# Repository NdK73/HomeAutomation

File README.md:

# HomeAutomation

This project consists of a protocol spec, the design files for physical nodes and the source code that glues it together.

## Protocol

[Full protocol description](protocol/protocol.txt) is available, together with examples of a [monitor](protocol/dom-monitor.py) and a [sender](protocol/dom-send.py). The protocol is text-based to ease debugging.

**ClearSky technology inside**: the basic concept is that **no coordinator** is needed for the nodes to work after the initial configuration. There must not be a single point of (catastrophic) failure. And obviously no "cloud" (hence **ClearSky**) service is needed either: you, and only you, decide if/when/which data can exit from your network!

The most critical element is currently the access point, that is so cheap that having a cold-standby one should not be a problem.

Messages must support authentication and encryption to guarantee that confidential packets or dangerous commands are actually sent from an authorized source.

**Warning**: protocol is still **work in progress** and **unstable**: non-backward-compatible changes are still possible! Only after 1.0.0 milestone changes that introduce incompatibilities will be delayed till 2.0.0 .

## HW

All HW designs were in [KiCAD](https://kicad.org/) 4.0.x (will follow what's packaged in latest [Ubuntu LTS](https://www.ubuntu.com/)) so not to require nonstandard installs. But 5.x introduced too many new features not to be used, and it's "easy enough" to install ([official instructions](https://kicad.org/download/ubuntu/)).

DIN-rail mounted devices are designed for the 6-modules [AK-DR-04C enclosure](https://www.aliexpress.com/item/-/1733706262.html). **Note:** these enclosures won't fit in a standard DIN rail box, unless you can move the rail further from the front panel (like in Gewiss GW40030).

Other devices are designed to be compatible with Vimar Plana series, but should fit other series with minor adjustements.

In the given layouts I use KF2EDGK **right-angle** (KF-2P, KF-4P or KF-6P) 5.08mm (or 3.81mm) pitch connectors so I can detach the node from power without having exposed wires with dangerous voltage laying around (and can reconnect it quickly and safely). Be sure to buy the angled version or you'll have a lot of extra work to bend the pins!

**Warning**: I did my best to keep the costs down without sacrificing security. Choice of the power brick is really important for security: **never** use HLK-PM01 clones unless you know what you're doing -- and even then it's better to avoid using 'em! If in doubt buy directly from [Hi-Link](http://www.hlktech.net/) (sorry, plain http, not https...). Probably the boards can't pass CE certification [only because of conducted emissions](https://skippy.org.uk/revisiting-the-hlk-pm01/), but since I don't have access to test equipment **use at your own risk** (or have 'em certified).

SSRs and relays should always be sourced from reputable sources. If in doubt, do not load 'em near the limits. For example never try a 400W load on a 2A SSR -- use a servo-relay. 2A SSRs are good for a couple of LED lamps, or a 40W bulb.

### [DomoNode](domonode) 1.1

A node based on ESP8266 to be mounted in a 6-modules DIN rail enclosure.

Provides 4 SSR outputs and an expansion bus connector.

[OSHW] IT000001 | [Certified open source hardware](https://oshwa.org/cert)

#### Errata

 - The text for GPIO4 and GPIO5 are reversed in the ESP12 symbol.

### [DomoNode 2](domonode2) 2.1 (WIP)

Evolution of DomoNode, but offers 6 inputs @ 230V, 6 SSR 2A@230V (each one have its own independent in and out lines, for maximum flexibility) and 8 independent LEDs, still in a 6-modules DIN rail enclosure. Kept SW compatibility with basic DomoNode (just the first 4 outputs), but different external connections.

To better follow the norms, now inputs are on the top and outputs at the bottom.

Same expansion bus connector as the DomoNode 1.1.

I kept 2mm between L and N lines and it **ought** to be double-insulation, but it's actually not required: the user can't touch anything that is not already expected to be at 230V (screws in connectors) without opening the enclosure (the expansion connector **MUST NOT** be exposed).

The board requires two v-cuts around the central part, drawn on ECO2 layer (but not visible in the image). Once the two boards gets separated, the smaller one have to be mounted over the bigger one, using 2 M3x25mm **plastic** spacers and suitable 1x14 pins headers (I used 2 1x14 female headers on the boards and 1x14 male pin strip with 21mm long pins to connect the two headers).

**Notes**:
 - Designed in KiCAD 5.1.5.
 - You can probably omit C8 quite safely

#### Errata

 - **Use 1k for R15-R22** or D1-D8 will burn after some months of use

#### Changes from (deprecated) [2.0](domonode2.0)
 - No glitches at powerup on outputs: all outputs are off until told otherwise by FW
 - Uses PCA9555 instead of MCP23017 (smaller, cheaper and already used for other expanders = smaller code footprint)
 - PCA9555 requires less components (pullups are included and outputs can directly drive SSRs)
 - wider traces (6mils were really too thin)
 - added socket for authentication chip (ATSHA204A or ATECC608A)
 - slightly moved connectors to better fit enclosure; probably some extra cuts to better accomodate connectors will be required anyway
 - replaced through-hole LEDs with SMD 0805 ones, better suited for light guides
 - highlighted pin 1 side for SMD IC footprints
 - corrected SDA and SCL pin assignment to use Wire.begin()
 - reduced confusing level semantics: relays and LEDs are ON when writing a HIGH level to the port (required to keep compatibility with FW for DomoNode 1.1), inputs are active when reading a LOW level (can be inverted via PCA9555)
 - used the PCB part with JLCPCB order number as a guide for LED holes: align "BASE" to the bottom of the concave part at the top of the box cover and use "LEDS CNTR" line to mark LEDs center line, then rotate the ruler and use markers on the short edges as a reference for the center line of the holes (the side opposite to "BASE" must be in contact with the right side of the concave part)
 - includes (yet untested) lightguides design files, ready to be sent to laser cutting service (use 5mm transparent plexiglas)
 - includes sample code (just add your FSM; webserver already accepts clicks on relay status to toggle it; config editing not yet implemented)

### [DomoNode-inout](domonode-inout) 1.1.1

An expansion node to be mounted in a 6-modules DIN rail enclosure.

Provides 4 SSR outputs, 3 220V opto-isolated inputs and 8 5V GPIOs.

Uses a PCA9555 for GPIOs and a 24C02 to store the expander config.

[OSHW] IT000002 | [Certified open source hardware](https://oshwa.org/cert)

### [DomoDisp](domodisp) 1.1

A node based on ESP8266 that provides physical user interface to the system.
Uses a 1.8" ST7735 LCD color display and a rotative encoder.
It is designed to be mounted either on the front of a DIN rail box, inside
a 4-modules Vimar Plana frame -- other frames could work but are untested, or
with the supplied enclosure in a 504 (4-modules) wall box.

Requires a 5V power source (possibly a DomoNode-inout, but a dedicated module
with power and relay will be published as soon as it's ready).

Includes sample "lib" for reading the encoder (needs cleanup... there still
are traces of experiments I did to read ESP's ADC from an interrupt routine).

The display can be managed by [TFT_eSPI](https://github.com/Bodmer/TFT_eSPI)
lib and works up to 27MHz (only 10MHz when testing on breadboard) -- remember
to edit User_setup.h before compiling your sketch!

[OSHW] IT000003 | [Certified open source hardware](https://oshwa.org/cert)

#### Errata

 - The text for GPIO4 and GPIO5 are reversed in the ESP12 symbol.

### [DomoDispV2](domodisp2) 2.0

**Future** release using shared SPI bus for display, freeing 2 GPIOs. One of
the freed GPIOs is used to control dimming.

**WARNING**: FW is incompatible with old DomoDisp!

### [DomoNode-inputs](domonode-inputs) 1.0

WIP - Still untested !

An expansion board with 11 inputs @ 220V and 5 low-voltage IOs.

When inputs are powered from 220V they get read as logic low.
Low-voltage inputs are directly connected to PCA9555 lines so there's a weak
(100k) pullup active at powerup. If you want to use 'em as outputs remember
to use inverted logic to avoid glitches at powerup.

### [DomoSwitch](domoswitch) 1.0

WIP / On hold (I'd need to source a suitable front panel, first)

A node that hosts 2 relays (or SSRs -- double footprint), 2 pushbuttons and 2
RGB LEDs. Split in 3 sub-boards to fit behind a 2-modules
[Vimar Plana 14042 hole cover](https://www.vimar.com/it/it/catalog/product/index/code/14042).

The buttons and LEDs are placed so that they match the markers inside the 14042
cover, simplifying the assemply.

To be compliant with SeeedFusion rules, I had to split the 3 sub boards as different designs.
Then I simply combined the sub-boards to better use the 100x100mm area. That means that for
$15 plus shipping I get 40 complete boards... I hope it doesn't require major mods!

**TODO**: support to enclose the dangerous sub-boards (I'll have to prototype it
with a 3D printer, but will need a resin cast for the final version).

### 3rd-party devices

It's obviously possible to support 3rd-party devices like SonOff, Shelly, touch switches and so on.
Reversing and further info is usually published first on [my site](https://csshl.net) (mostly Italian-only)

## SW

Still work in progress.

A sketch with [partial protocol implementation](https://github.com/NdK73/Domotic)
is under test.

Expansions (DomoNode-inout, DomoNode-inputs) are autodetected and (mostly)
autoconfigured by library. The algorithm is:
  - for each I2C bus address from 0x50 to 0x57
    - if slave found at 0x5X:
      - determine memory size:
        - try reading location 0-4 using 8-bit address (24LC02)
        - try re-reading the same locations, still using 8-bit addresses
        - both reads are equal => 8-bit addresses
        - else
          - set flag for 16-bit addresses
          - read locations 0-4 using 16-bit address (that would overwrite
          location 0 in 8-bit devices, but we already ruled out this
          is a 8-bit one...)
      - check first two bytes for 'magic' constant; if wrong, go to next
          address: not a device we can handle (possibly uninitialized)
      - read device config from it
    - if slave is not found at 0x5X, test if a slave is present at 0x2X
      (PCA9555 in DomoNode-inout 1.0)
      - if PCA9555 is found, create a fake config for 4 outs and 3 ins (TODO:
        how to handle other GPIOs?)
    - instantiate the correct device class

This algorithm assumes the memory have already been initialized.
The EEPROM must contain at least these 16 bytes:
  - 0x00 2 bytes 'magic' 0xD74A (0xD7 in 0x00 and 0x4A in 0x01)
  - 0x02 1 byte Expansion type (Official "registry" is kept in lib sources)
  - 0x03 1 byte Release code (every new HW release increments the release code)
  - 0x04 4 bytes "unique" board ID
  - 0x08 8 bytes reserved

The remaining space is used as defined by device class (usually for IO
configuration and descriptions).
The board ID must be "unique enough" so that the master node can detect that an
expansion have been changed and invalidate the old mappings.

## [Crypto HW](SecurityChips/)

I added to the repository all the informations I found re: security chips that could be used w/o signing NDAs. The list is probably incomplete.

I'm currently working on ATECC608A, trying to reverse engineer the information that would require signing NDA (why, Microchip? WHY??? you opened the docs for the 508...)

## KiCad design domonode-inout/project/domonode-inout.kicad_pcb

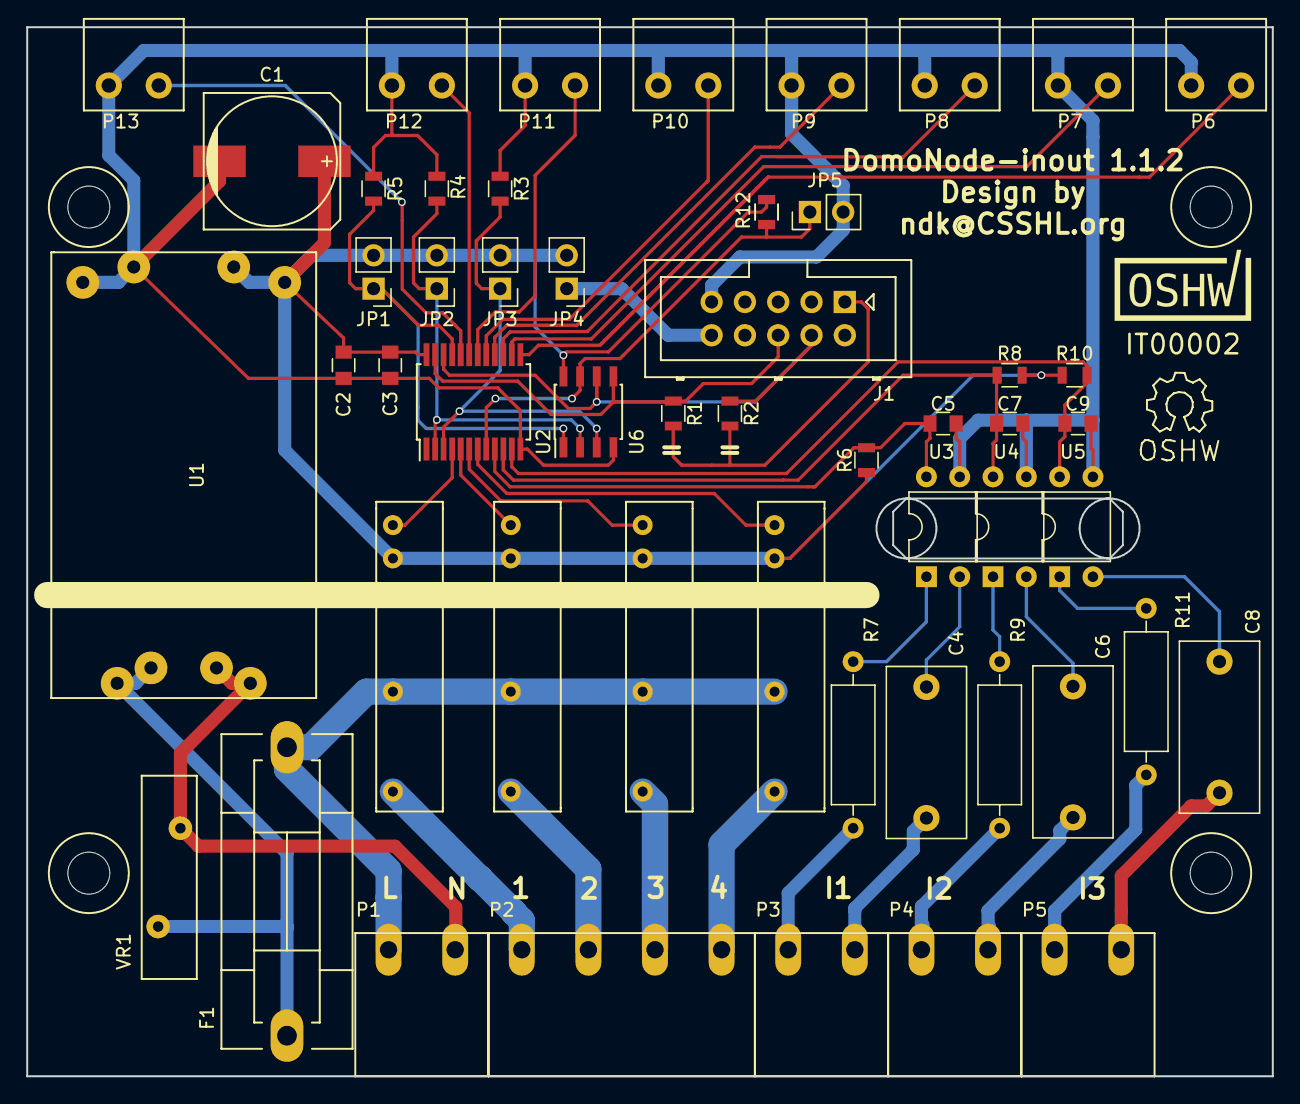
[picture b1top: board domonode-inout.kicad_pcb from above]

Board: 2 copper layers, 95.0 x 80.0 mm, 54 parts (0 on the bottom side), 44 nets.

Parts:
BOX: Enclosure_DIN_6p_nomargin
C1: C; c_elec_10x10
C2, C3: C; C_0805
C4, C6, C8: 0.1uF X2; C_Rect_L13.0mm_W6.0mm_P10.00mm_FKS3_FKP3_MKS4
C5, C7, C9: 1uF; C_0805
F1: FUSE; Fuseholder5x20_horiz_SemiClosed_Casing10x25mm
J1: CONN_2x5; Multicomp_MC9A12-1034_2x05x2.54mm_Straight
JP1, JP2, JP3: Jumper_NO_Small; Pin_Header_Straight_1x02_Pitch2.54mm
JP4, JP5: Jumper_NC_Small; Pin_Header_Straight_1x02_Pitch2.54mm
OSHW_Mono_0.25_Scale: IT00002; OSHW_Mono_0.25_Scale
P1, P3, P4, P5: CONN_01X02; KF2EDGK-5.08-2
P2: Conn_01x04; KF2EDGK-5.08-4
P6, P7, P8, P9, P10, P11, P12, P13: CONN_01X02; ScrewTerm_2x3.81_bigpads
R1, R2, R3, R4, R5, R6, R8, R10, R12: 10k; R_0805
R7, R9, R11: 1k; R_Axial_DIN0309_L9.0mm_D3.2mm_P12.70mm_Horizontal
RL1, RL2, RL3, RL4: Omron_G3MB-202; G3MB
U1: HLK-PM01; ACDC-HLK+ND
U2: PCA9555; SSOP-24_5.3x8.2mm_Pitch0.65mm
U3, U4, U5: TLP620; DIP-4_W7.62mm
U6: 24LC02; SOIC-8_3.9x4.9mm_Pitch1.27mm
VR1: VR; RV_Disc_D15.5_W4.2_P7.5

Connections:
+3V3: J1.1, R1.1, R2.1
+5V: C1.1, C2.1, C3.1, JP1.2, JP2.2, JP3.2, JP4.2, R6.1, R8.1, R10.1, R12.1, RL1.3, RL2.3, RL3.3, RL4.3, U1.4, U2.24, U6.8
/5VEXT: J1.10, JP4.1
/A0: JP1.1, R5.1, U2.21, U6.1
/A1: JP2.1, R4.1, U2.2, U6.2
/A2: JP3.1, R3.1, U2.3, U6.3
/I1L: P3.1, R7.2
/I1N: C4.2, P3.2
/I2L: P4.1, R9.2
/I2N: C6.2, P4.2
/I3L: P5.1, R11.2
/I3N: C8.2, P5.2
/IN1: C5.1, R6.2, U2.9, U3.4
/IN2: C7.1, R8.2, U2.10, U4.4
/IN3: C9.1, R10.2, U2.11, U5.4
/IO0: P6.2, U2.13
/IO1: P7.2, U2.14
/IO2: P8.2, U2.15
/IO3: P9.2, U2.16
/IO4: P10.2, U2.17
/IO5: P11.2, U2.18
/IO6: P12.2, U2.19
/IO7: P13.2, U2.20
/L: F1.2, P1.1, RL1.2, RL2.2, RL3.2, RL4.2
/N: P1.2, U1.2, VR1.1
/RL1: RL1.4, U2.4
/RL1P: P2.1, RL1.1
/RL2: RL2.4, U2.5
/RL2P: P2.2, RL2.1
/RL3: RL3.4, U2.6
/RL3P: P2.3, RL3.1
/RL4: RL4.4, U2.7
/RL4P: P2.4, RL4.1
/SCL: J1.4, R2.2, U2.22, U6.6
/SDA: J1.6, R1.2, U2.23, U6.5
/WP: JP5.1, R12.2, U2.8, U6.7
GND: C1.2, C2.2, C3.2, C5.2, C7.2, C9.2, J1.9, JP5.2, P6.1, P7.1, P8.1, P9.1, P10.1, P11.1, P12.1, P13.1, R3.2, R4.2, R5.2, U1.3, U2.12, U3.3, U4.3, U5.3, U6.4
unnamed: C4.1, U3.2
unnamed: C6.1, U4.2
unnamed: C8.1, U5.2
unnamed: F1.1, U1.1, VR1.2
unnamed: R7.1, U3.1
unnamed: R9.1, U4.1
unnamed: R11.1, U5.1

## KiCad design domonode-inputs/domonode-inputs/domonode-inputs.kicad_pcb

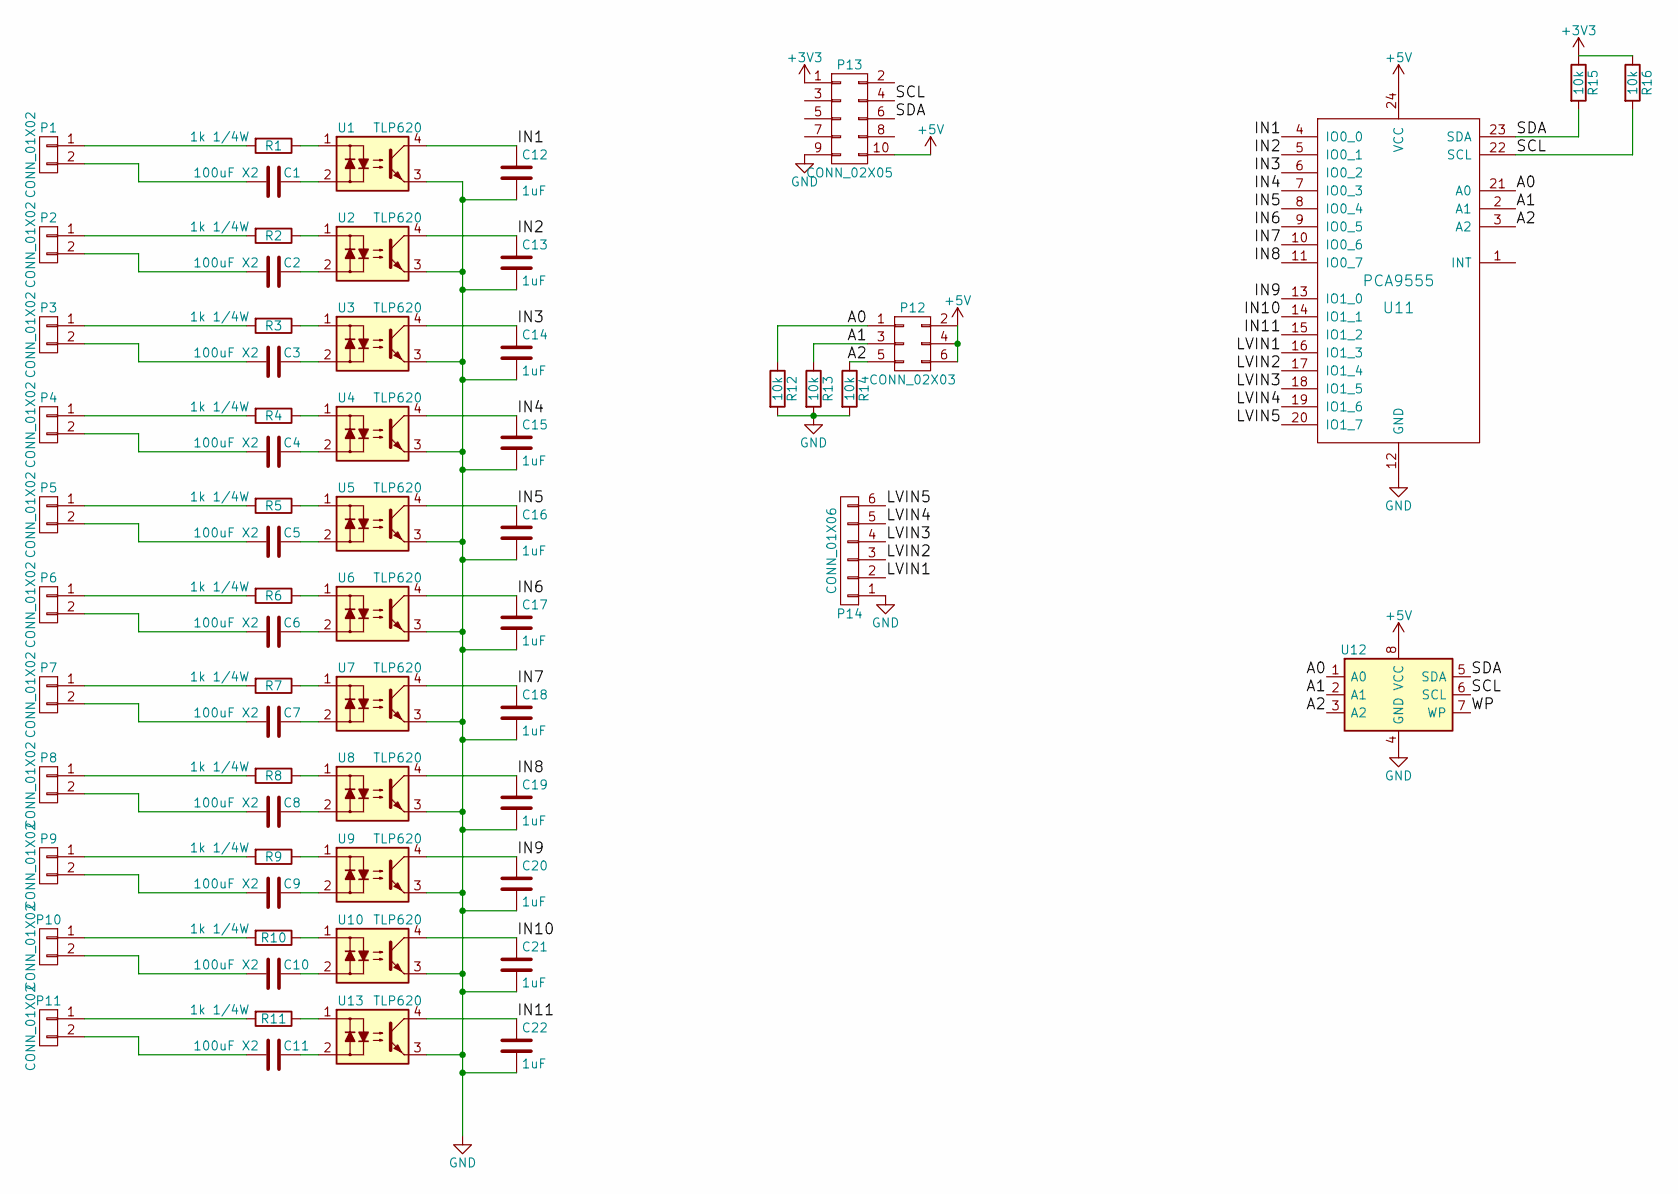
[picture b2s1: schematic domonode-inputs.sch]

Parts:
C1, C2, C3, C4, C5, C6, C7, C8, C9, C10, C11: 100uF X2; C_Rect_L13.0mm_W6.0mm_P10.00mm_FKS3_FKP3_MKS4
C12, C13, C14, C15, C16, C17, C18, C19, C20, C21, C22: 1uF; C_0805
P1, P2, P3, P4, P5, P6, P7, P8, P9, P10, P11: CONN_01X02; KF2EDGK-5.08-2
P12: CONN_02X03; Pin_Header_Straight_2x03_Pitch2.54mm
P13: CONN_02X05; Multicomp_MC9A12-1034_2x05x2.54mm_Straight
P14: CONN_01X06; Pin_Header_Straight_1x06
R1, R2, R3, R4, R5, R6, R7, R8, R9, R10, R11: 1k 1/4W; R_Axial_DIN0309_L9.0mm_D3.2mm_P12.70mm_Horizontal
R12, R13, R14, R15, R16: 10k; R_0805
U1, U2, U3, U4, U5, U6, U7, U8, U9, U10, U13: TLP620; DIP-4_W7.62mm_e_SOT-4
U11: PCA9555; SSOP-24_5.3x8.2mm_Pitch0.65mm
U12: 24LC02; SOIC-8_3.9x4.9mm_Pitch1.27mm

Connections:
+3V3: P13.1, R15.1, R16.1
+5V: P12.2, P12.4, P12.6, P13.10, U11.24 (VCC), U12.8 (VCC)
/A0: P12.1, R12.1, U11.21 (A0), U12.1 (A0)
/A1: P12.3, R13.1, U11.2 (A1), U12.2 (A1)
/A2: P12.5, R14.1, U11.3 (A2), U12.3 (A2)
/IN1: C12.1, U1.4, U11.4 (IO0_0)
/IN2: C13.1, U2.4, U11.5 (IO0_1)
/IN3: C14.1, U3.4, U11.6 (IO0_2)
/IN4: C15.1, U4.4, U11.7 (IO0_3)
/IN5: C16.1, U5.4, U11.8 (IO0_4)
/IN6: C17.1, U6.4, U11.9 (IO0_5)
/IN7: C18.1, U7.4, U11.10 (IO0_6)
/IN8: C19.1, U8.4, U11.11 (IO0_7)
/IN9: C20.1, U9.4, U11.13 (IO1_0)
/IN10: C21.1, U10.4, U11.14 (IO1_1)
/IN11: C22.1, U11.15 (IO1_2), U13.4
/LVIN1: P14.2, U11.16 (IO1_3)
/LVIN2: P14.3, U11.17 (IO1_4)
/LVIN3: P14.4, U11.18 (IO1_5)
/LVIN4: P14.5, U11.19 (IO1_6)
/LVIN5: P14.6, U11.20 (IO1_7)
/SCL: P13.4, R16.2, U11.22 (SCL), U12.6 (SCL)
/SDA: P13.6, R15.2, U11.23 (SDA), U12.5 (SDA)
GND: C12.2, C13.2, C14.2, C15.2, C16.2, C17.2, C18.2, C19.2, C20.2, C21.2, C22.2, P13.9, P14.1, R12.2, R13.2, R14.2, U1.3, U2.3, U3.3, U4.3, U5.3, U6.3, U7.3, U8.3, U9.3, U10.3, U11.12 (GND), U12.4 (GND), U13.3
unnamed: C1.1, U1.2
unnamed: C1.2, P1.2
unnamed: C2.1, U2.2
unnamed: C2.2, P2.2
unnamed: C3.1, U3.2
unnamed: C3.2, P3.2
unnamed: C4.1, U4.2
unnamed: C4.2, P4.2
unnamed: C5.1, U5.2
unnamed: C5.2, P5.2
unnamed: C6.1, U6.2
unnamed: C6.2, P6.2
unnamed: C7.1, U7.2
unnamed: C7.2, P7.2
unnamed: C8.1, U8.2
unnamed: C8.2, P8.2
unnamed: C9.1, U9.2
unnamed: C9.2, P9.2
unnamed: C10.1, U10.2
unnamed: C10.2, P10.2
unnamed: C11.1, U13.2
unnamed: C11.2, P11.2
unnamed: P1.1, R1.2
unnamed: P2.1, R2.2
unnamed: P3.1, R3.2
unnamed: P4.1, R4.2
unnamed: P5.1, R5.2
unnamed: P6.1, R6.2
unnamed: P7.1, R7.2
unnamed: P8.1, R8.2
unnamed: P9.1, R9.2
unnamed: P10.1, R10.2
unnamed: P11.1, R11.2
unnamed: R1.1, U1.1
unnamed: R2.1, U2.1
unnamed: R3.1, U3.1
unnamed: R4.1, U4.1
unnamed: R5.1, U5.1
unnamed: R6.1, U6.1
unnamed: R7.1, U7.1
unnamed: R8.1, U8.1
unnamed: R9.1, U9.1
unnamed: R10.1, U10.1
unnamed: R11.1, U13.1

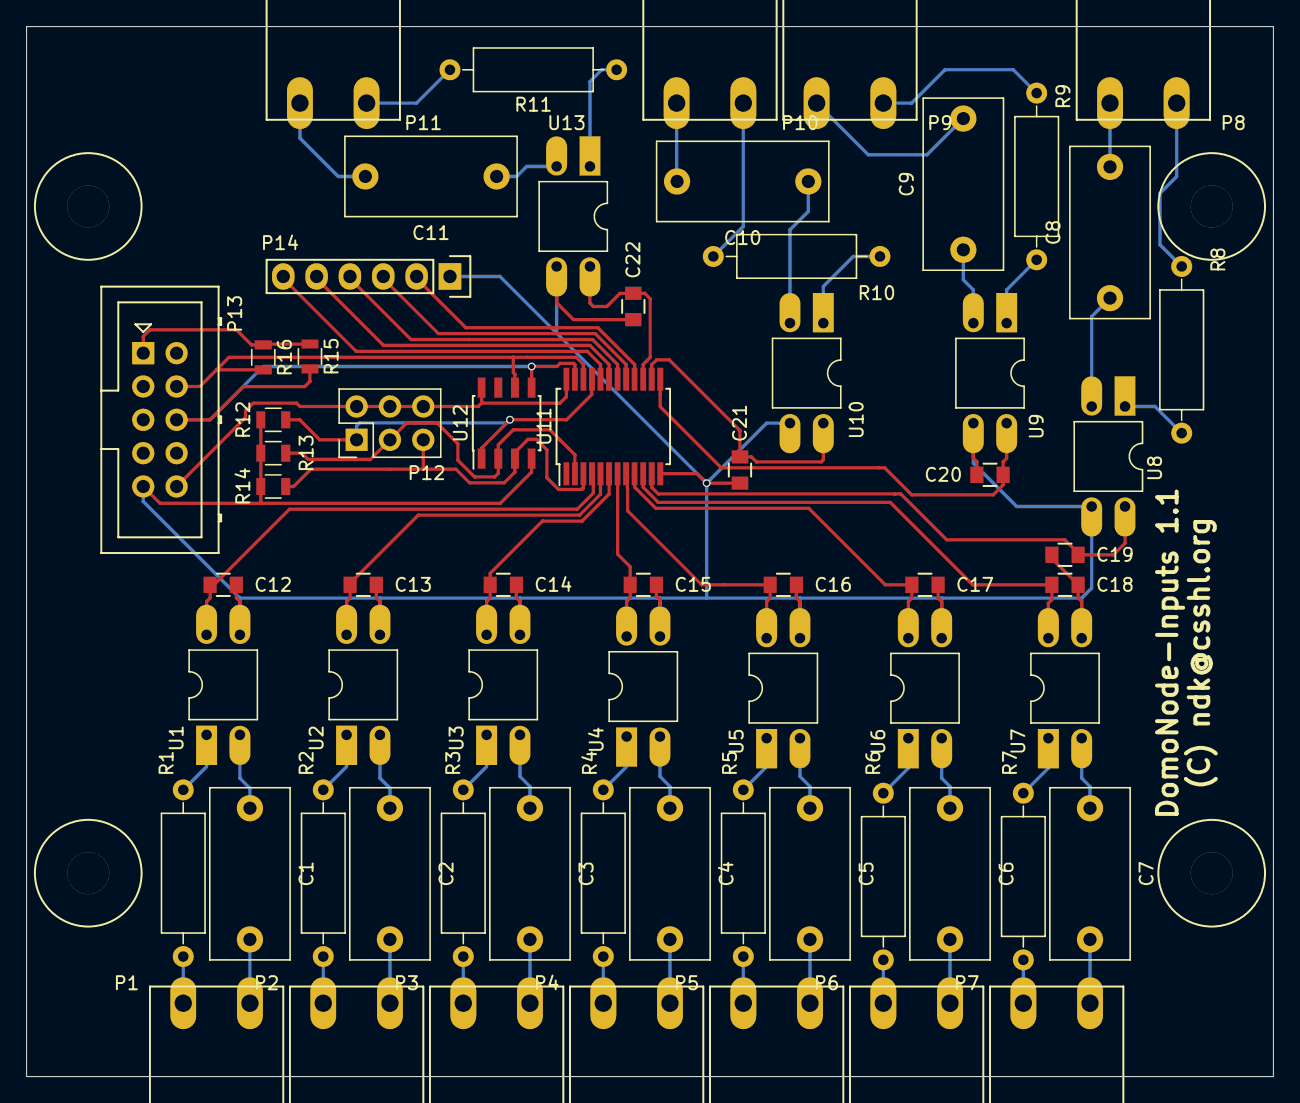
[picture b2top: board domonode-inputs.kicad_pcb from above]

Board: 2 copper layers, 95.0 x 80.0 mm, 66 parts (0 on the bottom side), 68 nets.

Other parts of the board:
BOX: Enclosure_DIN_6p

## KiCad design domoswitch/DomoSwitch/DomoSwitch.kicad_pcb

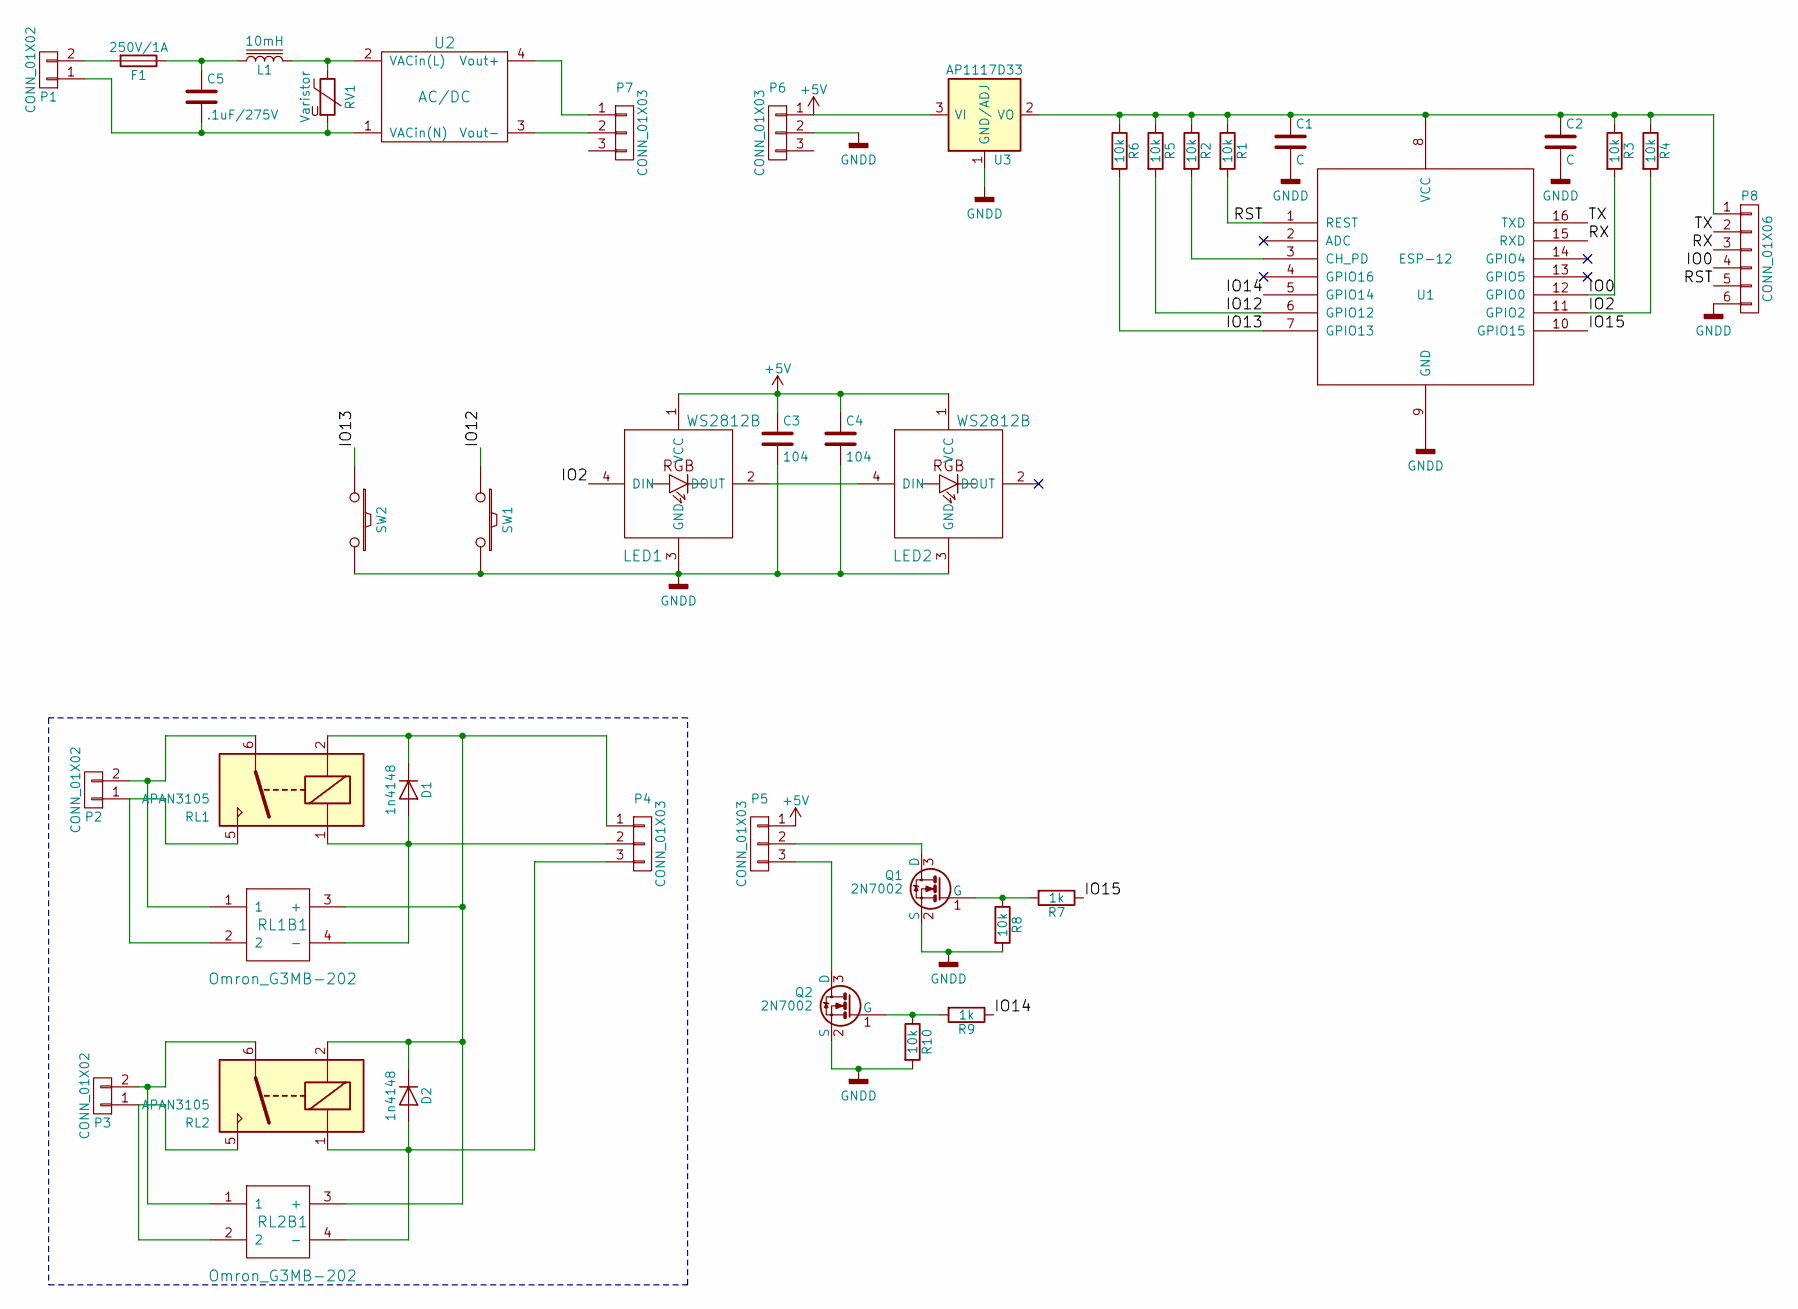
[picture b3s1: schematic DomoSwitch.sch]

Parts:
C1, C2: C; C_0805
C3, C4: 104; C_0805
C5: .1uF/275V; C_Rect_L13.0mm_W6.0mm_P10.00mm_FKS3_FKP3_MKS4
D1, D2: 1n4148; Diode_DO-41_SOD81_Vertical_KathodeUp
F1: 250V/1A; Fuse_SMD2920
L1: 10mH; CDRH127
LED1, LED2: WS2812B; ws2812b
P1, P2, P3: CONN_01X02; TerminalBlock_bornier-2_P5.08mm
P4, P5, P6, P7: CONN_01X03; Socket_Strip_Straight_1x03_Pitch2.54mm
P8: CONN_01X06; Socket_Strip_Straight_1x06
Q1, Q2: 2N7002; SOT-23
R1, R2, R3, R4, R5, R6, R8, R10: 10k; R_0805
R7, R9: 1k; R_0805
RL1, RL2: APAN3105; APAN31xx
RL1B1, RL2B1: Omron_G3MB-202; G3MB
RV1: Varistor; RV_Disc_D15.5_W4.2_P7.5
SW1, SW2: SW_PUSH; SW_SPST_FSMSM
U1: ESP-12; ESP-12-SMD
U2: AC/DC; HLK-PM01
U3: AP1117D33; SOT-223-3Lead_TabPin2

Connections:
+5V: C3.1, C4.1, LED1.1 (VCC), LED2.1 (VCC), P5.1, P6.1, U3.3 (VI)
/IO0: P8.4, R3.2, U1.12 (GPIO0)
/IO2: LED1.4 (DIN), R4.2, U1.11 (GPIO2)
/IO12: R5.2, SW1.1, U1.6 (GPIO12)
/IO13: R6.2, SW2.1, U1.7 (GPIO13)
/IO14: R9.1, U1.5 (GPIO14)
/IO15: R7.1, U1.10 (GPIO15)
/RST: P8.5, R1.2, U1.1 (REST)
/RX: P8.3, U1.15 (RXD)
/TX: P8.2, U1.16 (TXD)
GNDD: C1.2, C2.2, C3.2, C4.2, LED1.3 (GND), LED2.3 (GND), P6.2, P8.6, Q1.2 (S), Q2.2 (S), R8.2, R10.2, SW1.2, SW2.2, U1.9 (GND), U3.1 (GND/ADJ)
unnamed: C1.1, C2.1, P8.1, R1.1, R2.1, R3.1, R4.1, R5.1, R6.1, U1.8 (VCC), U3.2 (VO)
unnamed: C5.1, F1.1, L1.1
unnamed: C5.2, P1.1, RV1.2, U2.1 (VACin(N))
unnamed: D1.1 (K), D2.1 (K), P4.1, RL1.2, RL1B1.3 (+), RL2.2, RL2B1.3 (+)
unnamed: D1.2 (A), P4.2, RL1.1, RL1B1.4 (-)
unnamed: D2.2 (A), P4.3, RL2.1, RL2B1.4 (-)
unnamed: F1.2, P1.2
unnamed: L1.2, RV1.1, U2.2 (VACin(L))
unnamed: LED1.2 (DOUT), LED2.4 (DIN)
unnamed: P2.1, RL1.5, RL1B1.2
unnamed: P2.2, RL1.6, RL1B1.1
unnamed: P3.1, RL2.5, RL2B1.2
unnamed: P3.2, RL2.6, RL2B1.1
unnamed: P5.2, Q1.3 (D)
unnamed: P5.3, Q2.3 (D)
unnamed: P7.1, U2.4 (Vout+)
unnamed: P7.2, U2.3 (Vout-)
unnamed: Q1.1 (G), R7.2, R8.1
unnamed: Q2.1 (G), R9.2, R10.1
unnamed: R2.2, U1.3 (CH_PD)

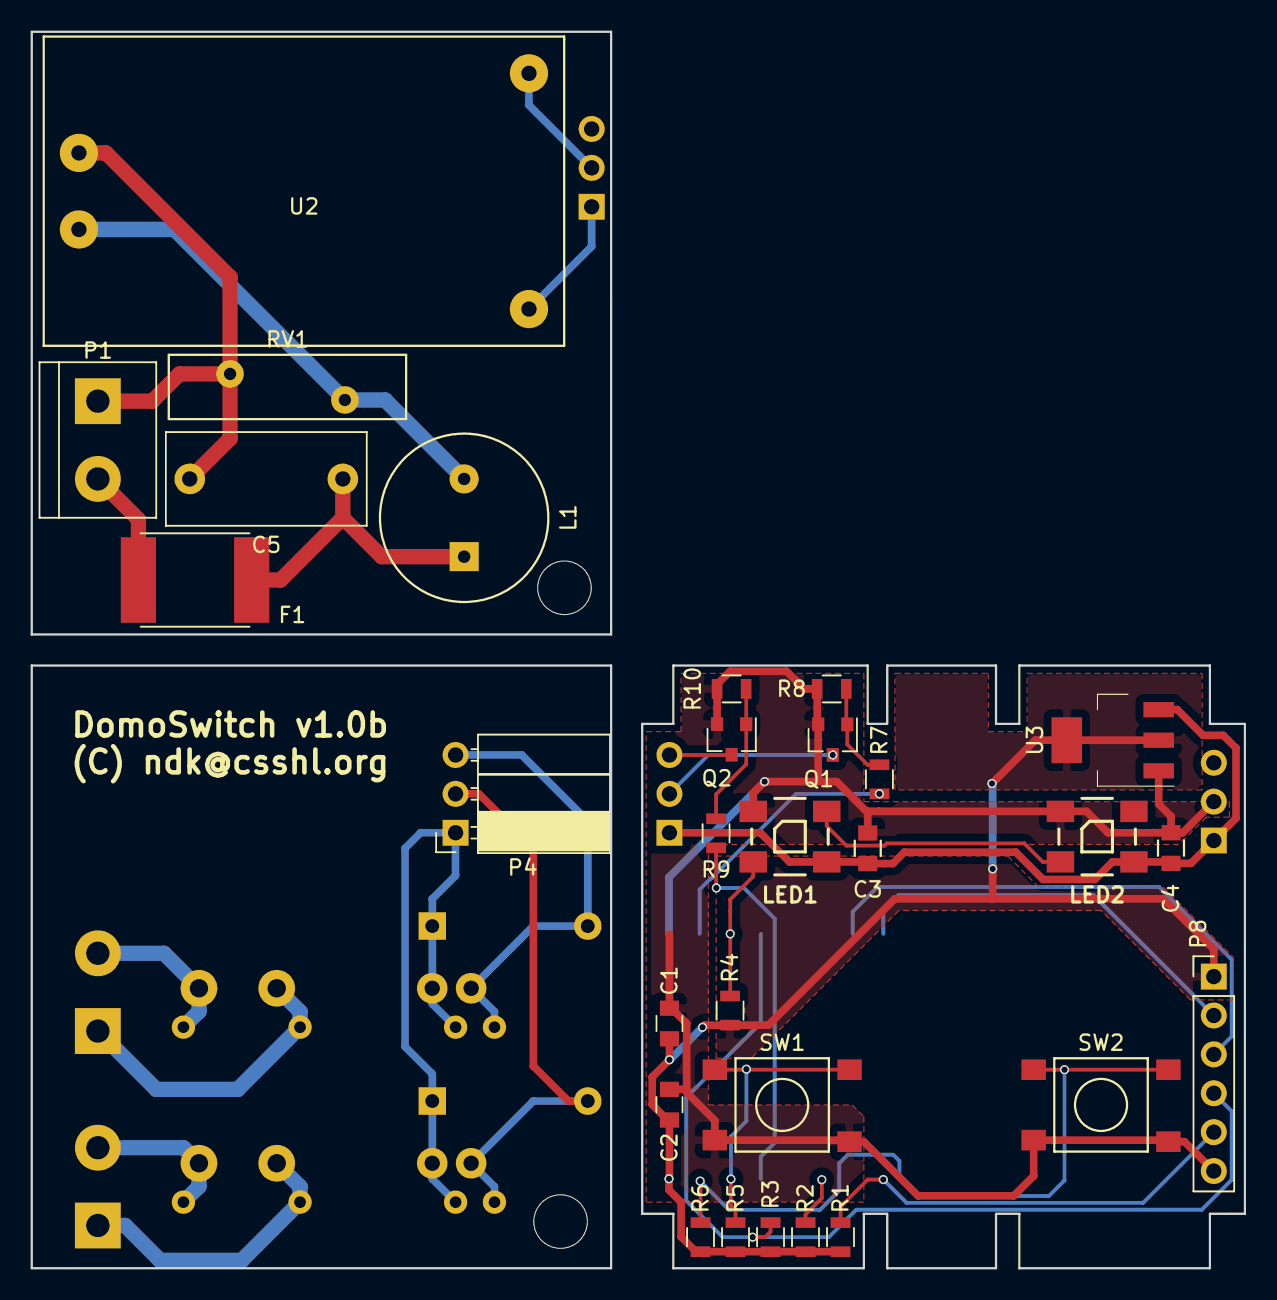
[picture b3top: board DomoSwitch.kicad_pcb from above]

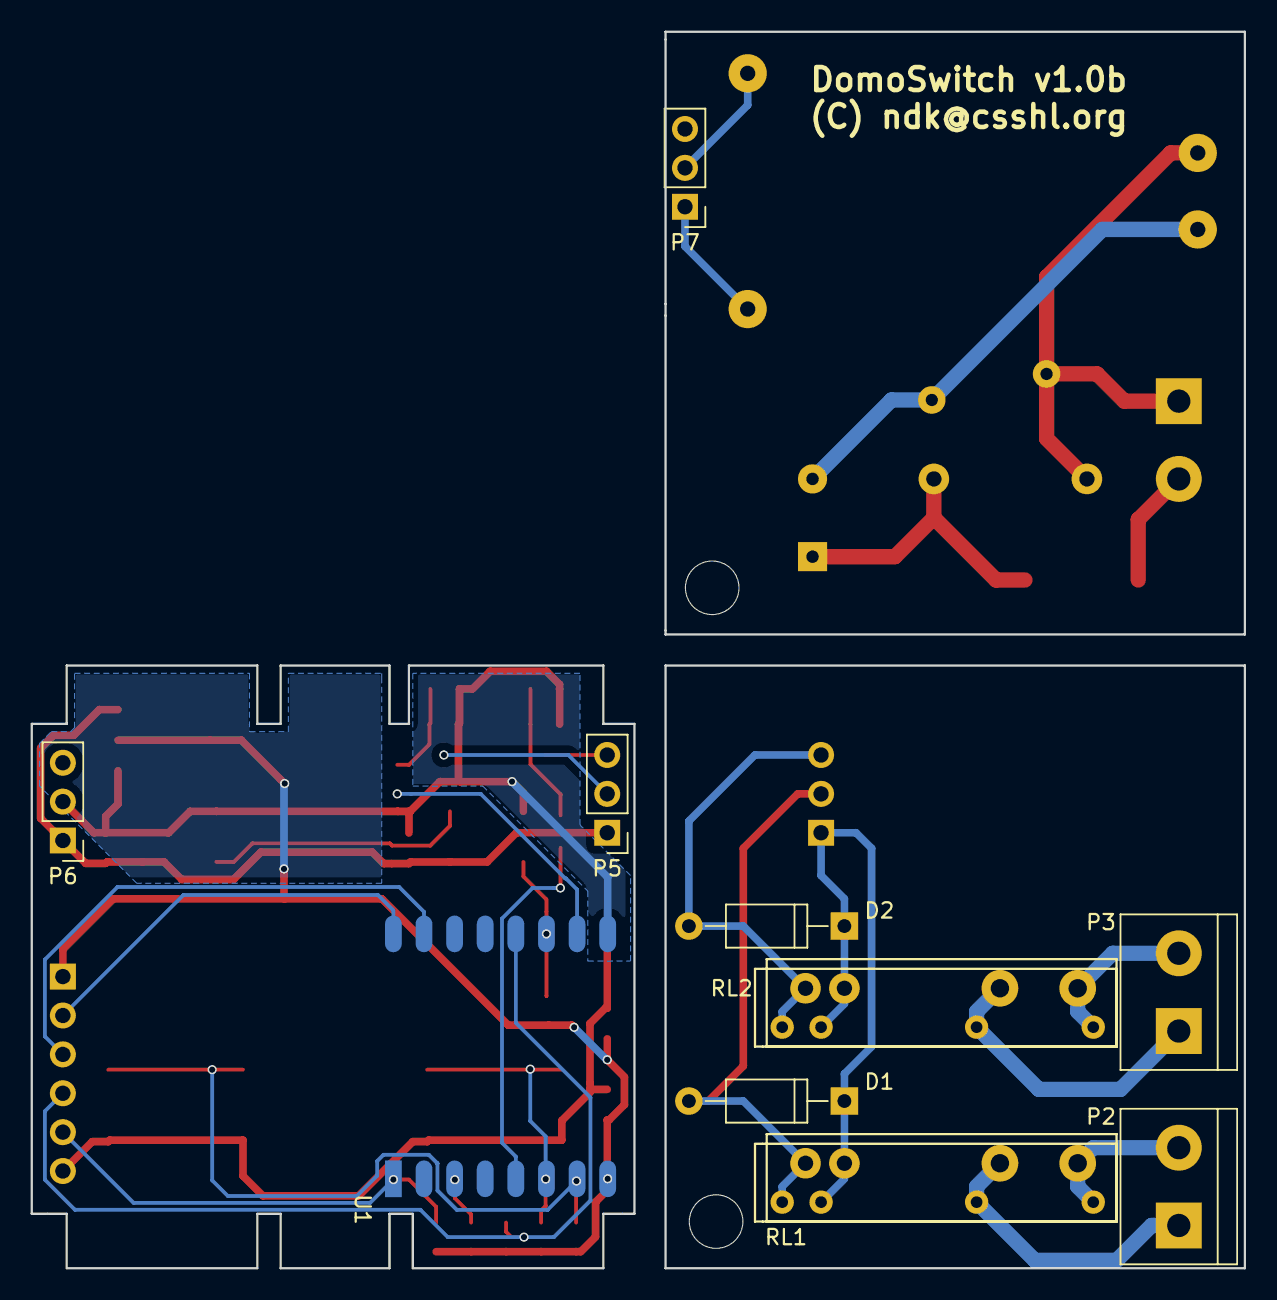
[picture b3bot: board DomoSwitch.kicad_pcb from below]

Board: 2 copper layers, 79.2 x 80.8 mm, 43 parts (12 on the bottom side), 31 nets.

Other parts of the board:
H1, H5: MountingHole_3-5mm

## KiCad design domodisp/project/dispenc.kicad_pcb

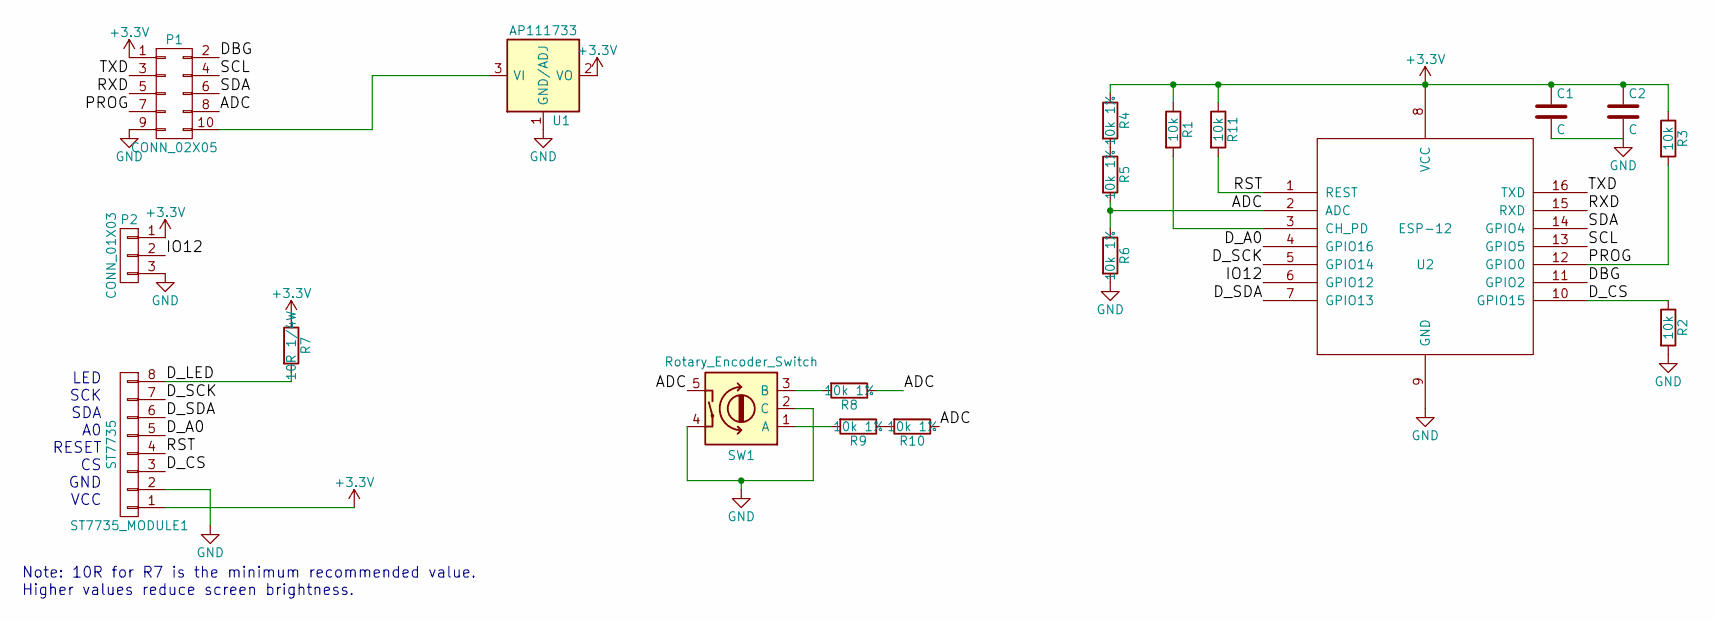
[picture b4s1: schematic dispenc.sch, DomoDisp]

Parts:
C1, C2: C; C_0805
P1: CONN_02X05; Multicomp_MC9A12-1034_2x05x2.54mm_Straight
P2: CONN_01X03; Pin_Header_Straight_1x03_Pitch2.54mm
R1, R2, R3, R11: 10k; R_0805
R4, R5, R6, R8, R9, R10: 10k 1%; R_0805
R7: 10R 1/4W; R_Axial_DIN0309_L9.0mm_D3.2mm_P12.70mm_Horizontal
ST7735_MODULE1: ST7735; ST7735_module
SW1: Rotary_Encoder_Switch; rotary-encoder
U1: AP111733; SOT-223
U2: ESP-12

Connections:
+3V3: C1.1, C2.1, P1.1, P2.1, R1.1, R3.1, R4.1, R7.1, R11.1, ST7735_MODULE1.1, U1.2 (VO), U1.4 (VO), U2.8 (VCC); also elsewhere on the board
+5V: P1.10, U1.3 (VI)
/ADC: P1.8, R5.2, R6.1, R8.1, R10.1, SW1.5, U2.2 (ADC)
/DBG: P1.2, U2.11 (GPIO2); also elsewhere on the board
/D_A0: ST7735_MODULE1.5, U2.4 (GPIO16)
/D_CS: R2.1, ST7735_MODULE1.3, U2.10 (GPIO15)
/D_LED: R7.2, ST7735_MODULE1.8
/D_SCK: ST7735_MODULE1.7, U2.5 (GPIO14)
/D_SDA: ST7735_MODULE1.6, U2.7 (GPIO13)
/IO12: P2.2, U2.6 (GPIO12)
/PROG: P1.7, R3.2, U2.12 (GPIO0)
/RST: R11.2, ST7735_MODULE1.4, U2.1 (REST)
/RXD: P1.5, U2.15 (RXD)
/SCL: P1.4, U2.13 (GPIO5)
/SDA: P1.6, U2.14 (GPIO4)
/TXD: P1.3, U2.16 (TXD)
GND: C1.2, C2.2, P1.9, P2.3, R2.2, R6.2, ST7735_MODULE1.2, SW1.2 (C), SW1.4, U1.1 (GND/ADJ), U2.9 (GND)
unnamed: R1.2, U2.3 (CH_PD)
unnamed: R4.2, R5.1
unnamed: R8.2, SW1.3 (B)
unnamed: R9.2, SW1.1 (A)
unnamed: R9.1, R10.2

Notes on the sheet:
LED SCK SDA A0 RESET CS GND VCC
Note: 10R for R7 is the minimum recommended value. Higher values reduce screen brightness.
